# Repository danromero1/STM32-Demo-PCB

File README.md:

# STM32 Demo PCB

My first end-to-end PCB design project - An STM32F103C8T6 development board for learning microcontroller hardware implementation and PCB design fundamentals.

---

## Overview

This project was my introduction to professional PCB design practices and microcontroller hardware implementation. The board features an STM32F103C8T6 MCU with external crystal oscillator, voltage regulation, and USB interface for programming and power delivery. The entire design was created in KiCAD following industry best practices for decoupling, signal routing, and design-for-manufacturability.

**Purpose:** Learn foundational PCB design skills and microcontroller hardware implementation  
**Outcome:** Complete 2-layer board design with manufacturing-ready Gerber files  
**Year:** 2023

---

## Design Features

**Microcontroller**
- STM32F103C8T6 (ARM Cortex-M3, 72 MHz)
- External 16 MHz crystal oscillator with load capacitance matching
- SWD/debug header for programming and debugging
- Boot mode selection

**Power Management**
- AMS1117-3.3V linear voltage regulator
- USB-powered (5V input)
- Ferrite bead filtering on VDDA (analog supply)
- Comprehensive decoupling capacitor network

**Interfaces**
- USB interface for programming and power
- SWD/JTAG debug header
- GPIO breakout headers
- I2C, SPI, UART accessible via headers

**PCB Design**
- 2-layer board layout
- Proper ground plane implementation
- Signal routing with impedance awareness
- ERC/DRC verification passed

---

## Technical Skills Demonstrated

**Schematic Design**
- Microcontroller peripheral connections
- Crystal oscillator design with load capacitance calculation
- Power supply design and voltage regulation
- USB interface implementation
- Reset and boot configuration circuits

**PCB Layout**
- Component placement optimization
- Signal routing and trace width selection
- Ground plane design and via placement
- Decoupling capacitor placement near power pins
- SWD/debug header routing
- Pick-and-place file generation

**Design Verification**
- Electrical Rule Check (ERC) compliance
- Design Rule Check (DRC) compliance
- Schematic-to-layout verification

---

## Design Process

### 1. Schematic Capture
Referenced STM32F103C8T6 datasheet and application notes to create a complete schematic including power, reset, clock, and USB circuitry.

### 2. Component Selection
- Selected AMS1117-3.3V for stable voltage regulation
- Calculated crystal load capacitors for 16 MHz oscillator
- Chose ferrite beads for analog/digital supply isolation

### 3. PCB Layout
- Created 2-layer stackup (signal/ground)
- Placed components with signal flow in mind
- Routed high-speed signals (USB, crystal) first
- Implemented ground plane with proper stitching vias
- Added silkscreen labels for all connectors

### 4. Manufacturing Preparation
- Generated Gerber files (RS-274X format)
- Created drill files and pick-and-place data
- Verified design against manufacturer capabilities

---

## Technical Specifications

**Microcontroller:** STM32F103C8T6 (ARM Cortex-M3, 72 MHz, 64KB Flash, 20KB RAM)  
**Clock:** 16 MHz external crystal oscillator  
**Power Input:** 5V via USB  
**Regulated Output:** 3.3V (AMS1117)  
**PCB:** 2-layer, standard FR4    
**Connector:** USB Type-B (or mini/micro - specify if known)

---

## Learning Outcomes

This project provided hands-on experience with:

**Hardware Design**
- STM32 microcontroller architecture and peripherals
- Clock circuitry and crystal oscillator design
- Power supply design and voltage regulation
- USB hardware implementation

**PCB Design Fundamentals**
- Schematic capture and component selection
- PCB layout and routing techniques
- Ground plane design and EMI mitigation
- Manufacturing file generation and validation
- Design rule verification (DRC/ERC)

**Professional Practices**
- Reading and interpreting datasheets
- Following application note guidelines
- Design-for-manufacturability principles
- Version control and documentation

---

## Project Files

- **Schematic:** Complete schematic design in KiCAD format
- **PCB Layout:** 2-layer board layout with ground plane
- **Gerber Files:** Manufacturing-ready RS-274X format

---

## Design Tools

- **KiCAD 6** - Schematic capture and PCB layout
- **Datasheets** - STM32F103C8T6, AMS1117, USB specifications
- **Application Notes** - STMicroelectronics hardware design guidelines

---

## Lessons Learned

**What Went Well:**
- Clean schematic organization and hierarchical design
- Proper decoupling capacitor placement
- Successful DRC/ERC verification

**Future Improvements:**
- Consider 4-layer stackup for better power distribution
- Add test points for critical signals
- Include LED indicators for power and status
- Optimize component placement for hand assembly

---

## Connection to Future Work

This project laid the foundation for more advanced designs:
- **Mixed-Signal Guitar Effects Pedal** - Applied layout techniques learned here to 4-layer mixed-signal design
- **Embedded Systems Projects** - Understanding of microcontroller hardware fundamentals
- **Power Supply Design** - Experience with voltage regulation and decoupling

The skills gained from this first PCB design directly enabled more complex projects involving high-speed signals, mixed-signal design, and multi-layer boards.

---

## Status

**Design Status:** Complete  
**Manufacturing:** Not fabricated (design exercise)  
**Testing:** N/A  
**Future Plans:** Foundational project - skills applied to advanced designs

---

## Contact

**Daniel Romero**  
Email: daniel.romero@ieee.org  
Portfolio: [electricalromero.com](https://electricalromero.com)  
LinkedIn: [linkedin.com/in/daniel-romero-ee](https://www.linkedin.com/in/daniel-romero-ee/)

---

*This was my first complete PCB design project, serving as a practical introduction to hardware design and manufacturing practices.*

*Last Updated: December 2024*

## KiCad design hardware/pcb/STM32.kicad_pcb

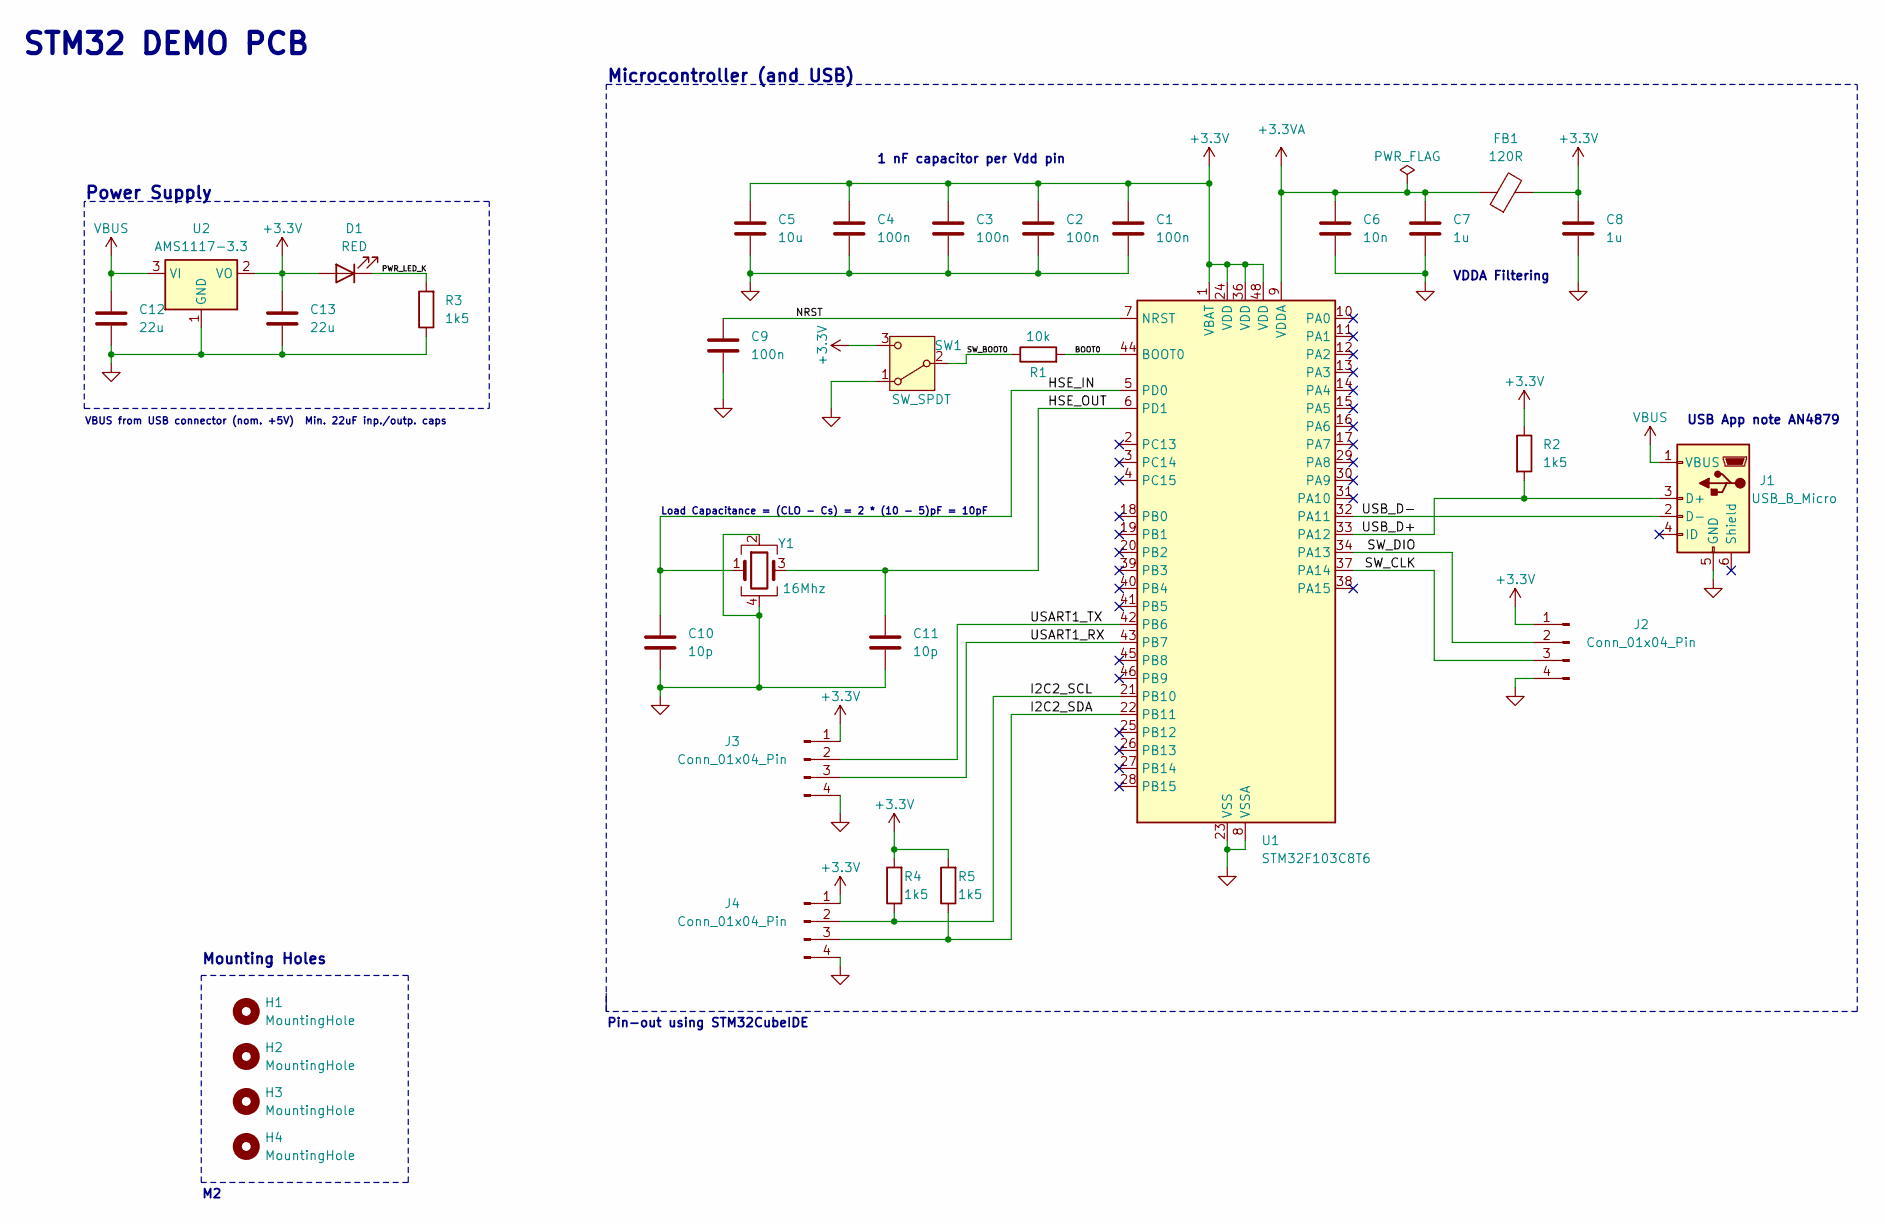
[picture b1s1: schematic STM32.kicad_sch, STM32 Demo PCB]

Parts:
C1, C2, C3, C4, C9: 100n; C_0402_1005Metric
C5: 10u; C_0603_1608Metric
C6: 10n; C_0603_1608Metric
C7, C8: 1u; C_0402_1005Metric
C10, C11: 10p; C_0402_1005Metric
C12, C13: 22u; C_0805_2012Metric
D1: RED; LED_0603_1608Metric
FB1: 120R; L_0603_1608Metric
H1, H2, H3, H4: MountingHole; MountingHole_2.2mm_M2
J1: USB_B_Micro; USB_Micro-B_Wuerth_629105150521
J2, J3, J4: Conn_01x04_Pin; PinHeader_1x04_P2.54mm_Vertical
R1: 10k; R_0402_1005Metric
R2, R3, R4, R5: 1k5; R_0402_1005Metric
SW1: SW_SPDT; SW_SPDT_PCM12
U1: STM32F103C8T6; LQFP-48_7x7mm_P0.5mm
U2: AMS1117-3.3; SOT-223-3_TabPin2
Y1: 16Mhz; Crystal_SMD_3225-4Pin_3.2x2.5mm

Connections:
+3.3V: C1.1, C2.1, C3.1, C4.1, C5.1, C8.1, C13.1, D1.2 (A), FB1.2, J2.1, J3.1, J4.1, R2.1, R4.2, R5.2, SW1.3 (C), U1.1 (VBAT), U1.24 (VDD), U1.36 (VDD), U1.48 (VDD), U2.2 (VO)
+3.3VA: C6.1, C7.1, FB1.1, U1.9 (VDDA)
/BOOT0: R1.2, U1.44 (BOOT0)
/HSE_IN: C10.1, U1.5 (PD0), Y1.1
/HSE_OUT: C11.1, U1.6 (PD1), Y1.3
/I2C2_SCL: J4.2, R4.1, U1.21 (PB10)
/I2C2_SDA: J4.3, R5.1, U1.22 (PB11)
/NRST: C9.1, U1.7 (NRST)
/PWR_LED_K: D1.1 (K), R3.2
/SW_BOOT0: R1.1, SW1.2 (B)
/SW_CLK: J2.3, U1.37 (PA14)
/SW_DIO: J2.2, U1.34 (PA13)
/USART1_RX: J3.3, U1.43 (PB7)
/USART1_TX: J3.2, U1.42 (PB6)
/USB_D+: J1.3 (D+), R2.2, U1.33 (PA12)
/USB_D-: J1.2 (D-), U1.32 (PA11)
GND: C1.2, C2.2, C3.2, C4.2, C5.2, C6.2, C7.2, C8.2, C9.2, C10.2, C11.2, C12.2, C13.2, J1.5 (GND), J2.4, J3.4, J4.4, R3.1, SW1.1 (A), U1.8 (VSSA), U1.23 (VSS), U1.35 (VSS), U1.47 (VSS), U2.1 (GND), Y1.2, Y1.4
VBUS: C12.1, J1.1 (VBUS), U2.3 (VI)

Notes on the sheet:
VDDA Filtering
1 nF capacitor per Vdd pin
Pin-out using STM32CubeIDE
STM32 DEMO PCB
VBUS from USB connector (nom. +5V) Min. 22uF inp./outp. caps
Microcontroller (and USB)
Mounting Holes
Load Capacitance = (CLO - Cs) = 2 * (10 - 5)pF = 10pF
USB App note AN4879
Power Supply

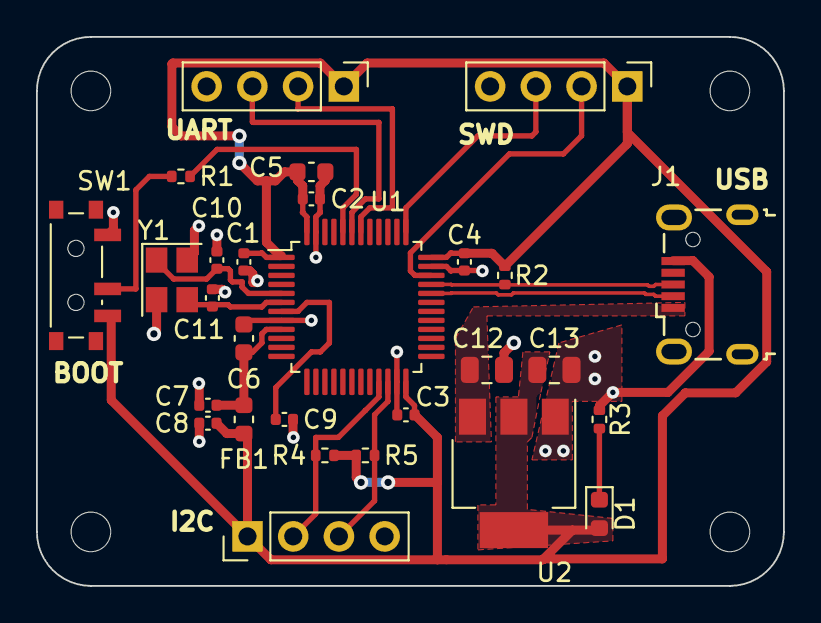
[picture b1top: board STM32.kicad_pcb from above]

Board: 2 copper layers, 41.5 x 30.5 mm, 32 parts (0 on the bottom side), 18 nets.
